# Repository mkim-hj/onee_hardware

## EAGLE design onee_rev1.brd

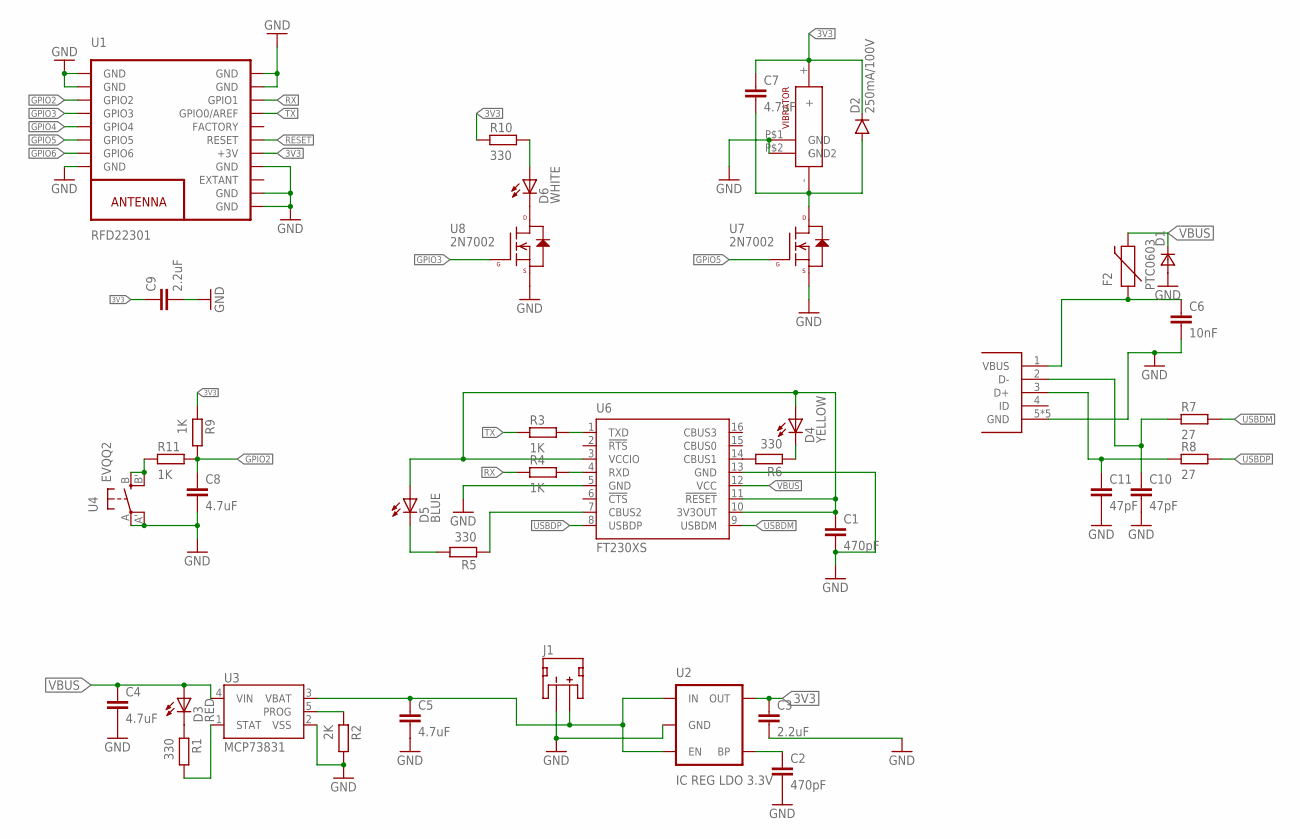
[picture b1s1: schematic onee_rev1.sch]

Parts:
C1, C2: 470pF; 0603-CAP
C3, C9: 2.2uF; 0603-CAP
C4, C5, C7, C8: 4.7uF; 0603-CAP
C6: 10nF; 0603-CAP
C10, C11: 47pF; 0603-CAP
D1: DSOD323; SOD323
D2: 250mA/100V; SOD-323
D3: RED; CHIP-LED0805
D4: YELLOW; CHIP-LED0805
D5: BLUE; CHIP-LED0805
D6: WHITE; LED_SML0603
F2: PTC0603; 0603
J1: BATTERY; JST-2-SMD
R1, R5, R6, R10: 330; R0603
R2: 2K; R0603
R3, R4, R9, R11: 1K; R0603
R7, R8: 27; R0603
U1: RFD22301
U2: IC REG LDO 3.3V; SOT23-5
U3: MCP73831; SOT23-5
U4: EVQQ2; EVQ-Q2
U5: USB_MICROB
U6: FT230XS; SSOP16
U7, U8: 2N7002; SOT23-3
U$2: 304-100

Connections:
3V3: C3.1, C7.1, C9.1, D2.C, R9.1, R10.1, U1.13 (+3V), U2.5 (OUT), U$2.+
GND: C1.2, C2.2, C3.2, C4.2, C5.2, C6.2, C8.2, C9.2, C10.2, C11.2, D1.2 (A), J1.1 (-), R2.2, U1.1 (GND), U1.2 (GND), U1.8 (GND), U1.9 (GND), U1.10 (GND), U1.12 (GND), U1.18 (GND), U1.19 (GND), U2.2 (GND), U3.2 (VSS), U4.A, U4.A' (P1), U5.5 (GND), U5.P$6 (GND), U5.P$7 (GND), U5.P$8 (GND), U5.P$9 (GND), U6.5 (GND), U6.13 (GND), U7.2 (S), U8.2 (S), U$2.P$1 (GND), U$2.P$2 (GND2)
GPIO2: C8.1, R9.2, R11.2, U1.3 (GPIO2)
GPIO3: U1.4 (GPIO3), U8.1 (G)
GPIO4: U1.5 (GPIO4)
GPIO5: U1.6 (GPIO5), U7.1 (G)
GPIO6: U1.7 (GPIO6)
unnamed: R3.2, U6.1 (TXD)
unnamed: C2.1, U2.4 (BP)
unnamed: R4.2, U6.4 (RXD)
unnamed: R2.1, U3.5 (PROG)
unnamed: R6.2, U6.14 (CBUS1)
unnamed: D5.C, R5.2
unnamed: C1.1, D4.A, D5.A, U6.3 (VCCIO), U6.10 (3V3OUT), U6.11 (!RESET)
unnamed: D3.C, R1.1
unnamed: R1.2, U3.1 (STAT)
unnamed: D4.C, R6.1
unnamed: R5.1, U6.7 (CBUS2)
unnamed: D6.C, U8.3 (D)
unnamed: D6.A, R10.2
unnamed: C10.1, R7.1, U5.2 (D-)
unnamed: C11.1, R8.1, U5.3 (D+)
unnamed: C6.1, F2.1, U5.1 (VBUS)
unnamed: C7.2, D2.A, U7.3 (D), U$2.-
unnamed: R11.1, U4.B (S), U4.B' (S1)
POWER: C5.1, J1.2 (+), U2.1 (IN), U2.3 (EN), U3.3 (VBAT)
RESET: U1.14 (RESET)
RX: R4.1, U1.17 (GPIO1)
TX: R3.1, U1.16 (GPIO0/AREF)
USBDM: R7.2, U6.9 (USBDM)
USBDP: R8.2, U6.8 (USBDP)
VBUS: C4.1, D1.1 (C), D3.A, F2.2, U3.4 (VIN), U6.12 (VCC)

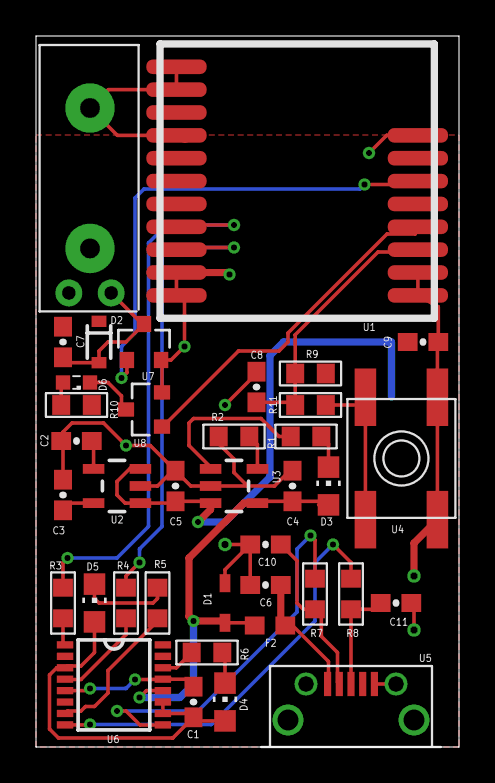
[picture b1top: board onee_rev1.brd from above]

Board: 2 copper layers, 23.5 x 39.5 mm, 39 parts (1 on the bottom side), 29 nets.

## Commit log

2016-06-08 board files

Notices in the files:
parts and their libraries:
SparkFun-PowerIC: Licensing: Creative Commons ShareAlike 4.0 International - https://creativecommons.org/licenses/by-sa/4.0
